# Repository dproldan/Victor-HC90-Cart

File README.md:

# Victor-HC90-Cart
Victor HC-9x adaptor from internal xpansion bus to 50 pin cartridge slot

This has not been manufactured yet.

This is a reproduction from a PCB picture posted here:
https://www.msx.org/forum/msx-talk/hardware/what-is-this-victor-hc-9x-home-made-extension-card-used-for

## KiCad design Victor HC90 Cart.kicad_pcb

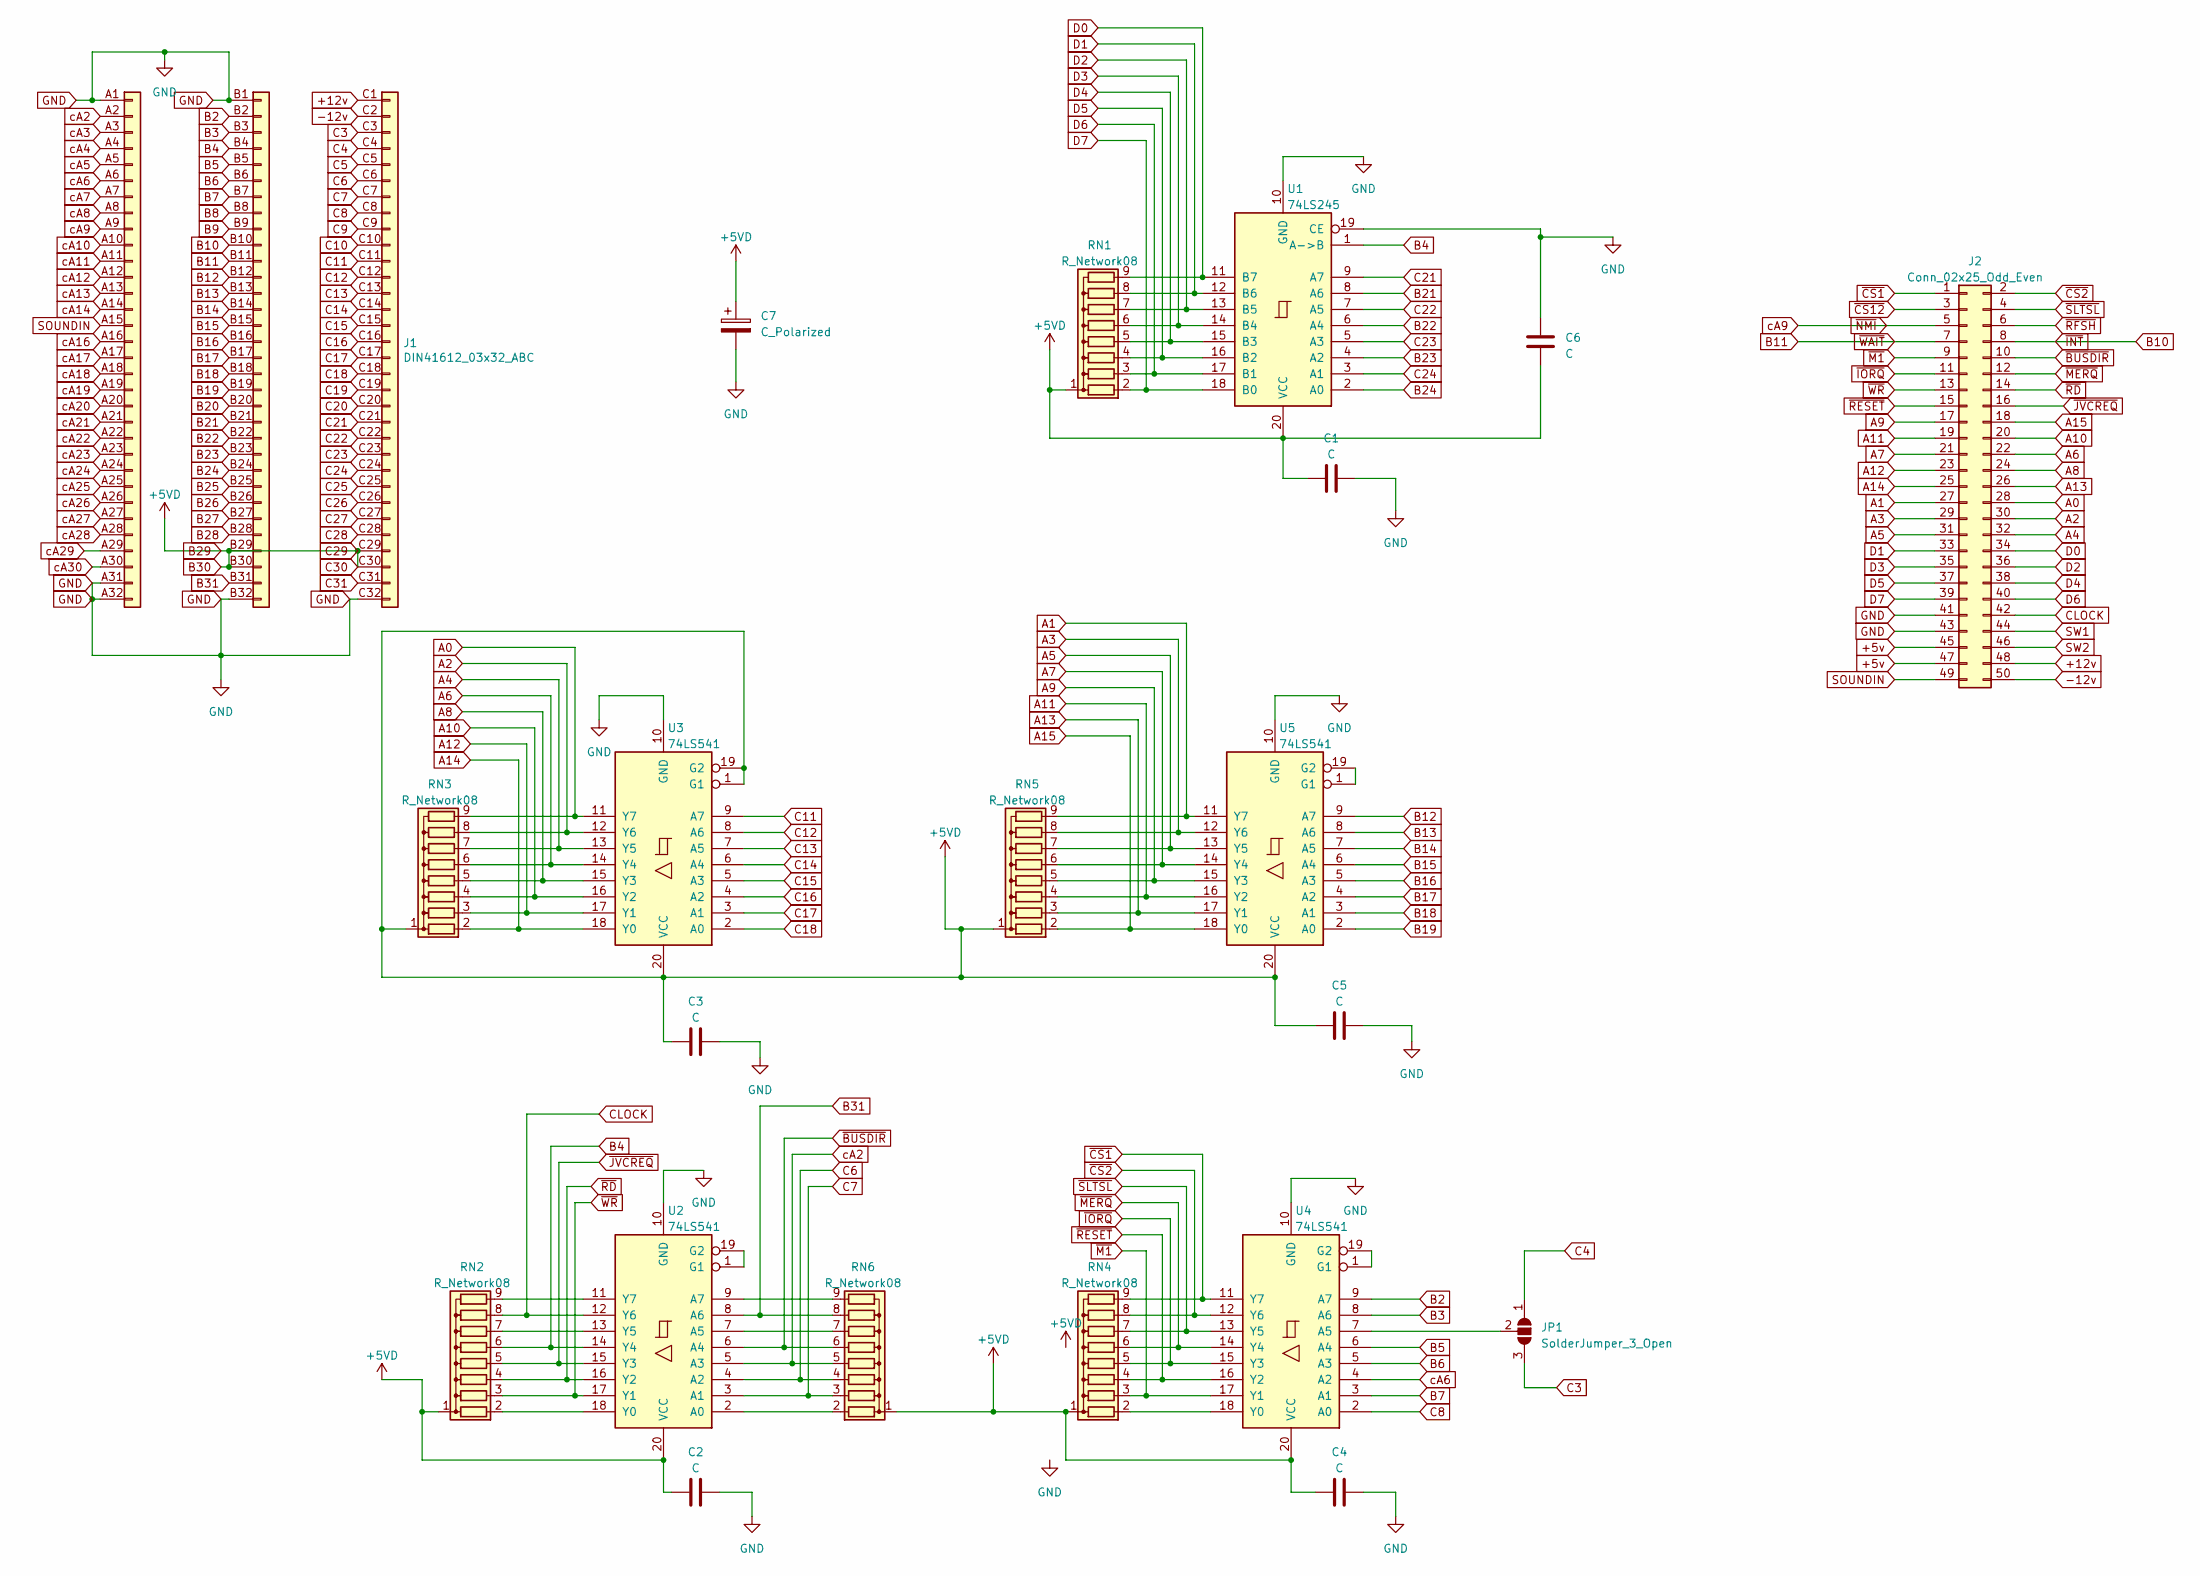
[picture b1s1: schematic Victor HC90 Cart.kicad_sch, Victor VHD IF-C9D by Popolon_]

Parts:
C1, C2, C3, C4, C5, C6: C; C_Disc_D4.3mm_W1.9mm_P5.00mm
C7: C_Polarized; CP_Radial_D8.0mm_P2.50mm
J1: DIN41612_03x32_ABC; Conn_DIN41612_B096F
J2: Conn_02x25_Odd_Even; IDC-Header_2x25_P2.54mm_Latch_Horizontal
JP1: SolderJumper_3_Open; SolderJumper-3_P1.3mm_Open_RoundedPad1.0x1.5mm
RN1, RN2, RN3, RN4, RN5, RN6: R_Network08; R_Array_SIP9
U1: 74LS245; DIP-20_W7.62mm_LongPads
U2, U3, U4, U5: 74LS541; DIP-20_W7.62mm_LongPads

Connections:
+5v: J2.45, J2.47
+12v: J1.C1 (Pin_c1), J2.48
-12v: J1.C2 (Pin_c2), J2.50
A0: J2.28, RN3.9 (R8), U3.11 (Y7)
A1: J2.27, RN5.9 (R8), U5.11 (Y7)
A2: J2.30, RN3.8 (R7), U3.12 (Y6)
A3: J2.29, RN5.8 (R7), U5.12 (Y6)
A4: J2.32, RN3.7 (R6), U3.13 (Y5)
A5: J2.31, RN5.7 (R6), U5.13 (Y5)
A6: J2.22, RN3.6 (R5), U3.14 (Y4)
A7: J2.21, RN5.6 (R5), U5.14 (Y4)
A8: J2.24, RN3.5 (R4), U3.15 (Y3)
A9: J2.17, RN5.5 (R4), U5.15 (Y3)
A10: J2.20, RN3.4 (R3), U3.16 (Y2)
A11: J2.19, RN5.4 (R3), U5.16 (Y2)
A12: J2.23, RN3.3 (R2), U3.17 (Y1)
A13: J2.26, RN5.3 (R2), U5.17 (Y1)
A14: J2.25, RN3.2 (R1), U3.18 (Y0)
A15: J2.18, RN5.2 (R1), U5.18 (Y0)
B2: J1.B2 (Pin_b2), U4.9 (A7)
B3: J1.B3 (Pin_b3), U4.8 (A6)
B4: J1.B4 (Pin_b4), RN2.6 (R5), U1.1 (A->B), U2.14 (Y4)
B5: J1.B5 (Pin_b5), U4.6 (A4)
B6: J1.B6 (Pin_b6), U4.5 (A3)
B7: J1.B7 (Pin_b7), U4.3 (A1)
B8: J1.B8 (Pin_b8)
B9: J1.B9 (Pin_b9)
B10: J1.B10 (Pin_b10), J2.8
B11: J1.B11 (Pin_b11), J2.7
B12: J1.B12 (Pin_b12), U5.9 (A7)
B13: J1.B13 (Pin_b13), U5.8 (A6)
B14: J1.B14 (Pin_b14), U5.7 (A5)
B15: J1.B15 (Pin_b15), U5.6 (A4)
B16: J1.B16 (Pin_b16), U5.5 (A3)
B17: J1.B17 (Pin_b17), U5.4 (A2)
B18: J1.B18 (Pin_b18), U5.3 (A1)
B19: J1.B19 (Pin_b19), U5.2 (A0)
B20: J1.B20 (Pin_b20)
B21: J1.B21 (Pin_b21), U1.8 (A6)
B22: J1.B22 (Pin_b22), U1.6 (A4)
B23: J1.B23 (Pin_b23), U1.4 (A2)
B24: J1.B24 (Pin_b24), U1.2 (A0)
B25: J1.B25 (Pin_b25)
B26: J1.B26 (Pin_b26)
B27: J1.B27 (Pin_b27)
B28: J1.B28 (Pin_b28)
B29: C1.1, C2.1, C3.1, C4.1, C5.1, C6.1, C7.1, J1.B29 (Pin_b29), J1.B30 (Pin_b30), J1.C29 (Pin_c29), J1.C30 (Pin_c30), RN1.1 (common), RN2.1 (common), RN3.1 (common), RN4.1 (common), RN5.1 (common), RN6.1 (common), U1.20 (VCC), U2.20 (VCC), U3.1 (G1), U3.19 (G2), U3.20 (VCC), U4.20 (VCC), U5.20 (VCC)
B31: J1.B31 (Pin_b31), RN6.8 (R7), U2.8 (A6)
C3: J1.C3 (Pin_c3), JP1.3 (B)
C4: J1.C4 (Pin_c4), JP1.1 (A)
C5: J1.C5 (Pin_c5)
C6: J1.C6 (Pin_c6), RN6.4 (R3), U2.4 (A2)
C7: J1.C7 (Pin_c7), RN6.3 (R2), U2.3 (A1)
C8: J1.C8 (Pin_c8), U4.2 (A0)
C9: J1.C9 (Pin_c9)
C10: J1.C10 (Pin_c10)
C11: J1.C11 (Pin_c11), U3.9 (A7)
C12: J1.C12 (Pin_c12), U3.8 (A6)
C13: J1.C13 (Pin_c13), U3.7 (A5)
C14: J1.C14 (Pin_c14), U3.6 (A4)
C15: J1.C15 (Pin_c15), U3.5 (A3)
C16: J1.C16 (Pin_c16), U3.4 (A2)
C17: J1.C17 (Pin_c17), U3.3 (A1)
C18: J1.C18 (Pin_c18), U3.2 (A0)
C19: J1.C19 (Pin_c19)
C20: J1.C20 (Pin_c20)
C21: J1.C21 (Pin_c21), U1.9 (A7)
C22: J1.C22 (Pin_c22), U1.7 (A5)
C23: J1.C23 (Pin_c23), U1.5 (A3)
C24: J1.C24 (Pin_c24), U1.3 (A1)
C25: J1.C25 (Pin_c25)
C26: J1.C26 (Pin_c26)
C27: J1.C27 (Pin_c27)
C28: J1.C28 (Pin_c28)
C31: J1.C31 (Pin_c31)
CLOCK: J2.42, RN2.8 (R7), U2.12 (Y6)
D0: J2.34, RN1.9 (R8), U1.11 (B7)
D1: J2.33, RN1.8 (R7), U1.12 (B6)
D2: J2.36, RN1.7 (R6), U1.13 (B5)
D3: J2.35, RN1.6 (R5), U1.14 (B4)
D4: J2.38, RN1.5 (R4), U1.15 (B3)
D5: J2.37, RN1.4 (R3), U1.16 (B2)
D6: J2.40, RN1.3 (R2), U1.17 (B1)
D7: J2.39, RN1.2 (R1), U1.18 (B0)
GND: C1.2, C2.2, C3.2, C4.2, C5.2, C6.2, C7.2, J1.A1 (Pin_a1), J1.A31 (Pin_a31), J1.A32 (Pin_a32), J1.B1 (Pin_b1), J1.B32 (Pin_b32), J1.C32 (Pin_c32), J2.41, J2.43, U1.10 (GND), U1.19 (CE), U2.10 (GND), U3.10 (GND), U4.10 (GND), U5.10 (GND)
unnamed: JP1.2 (C), U4.7 (A5)
unnamed: RN2.2 (R1), U2.18 (Y0)
unnamed: RN2.7 (R6), U2.13 (Y5)
unnamed: RN2.9 (R8), U2.11 (Y7)
unnamed: RN4.2 (R1), U4.18 (Y0)
unnamed: RN6.2 (R1), U2.2 (A0)
unnamed: RN6.7 (R6), U2.7 (A5)
unnamed: RN6.9 (R8), U2.9 (A7)
unnamed: U2.1 (G1), U2.19 (G2)
unnamed: U4.1 (G1), U4.19 (G2)
unnamed: U5.1 (G1), U5.19 (G2)
SOUNDIN: J1.A15 (Pin_a15), J2.49
SW1: J2.44
SW2: J2.46
cA2: J1.A2 (Pin_a2), RN6.5 (R4), U2.5 (A3)
cA3: J1.A3 (Pin_a3)
cA4: J1.A4 (Pin_a4)
cA5: J1.A5 (Pin_a5)
cA6: J1.A6 (Pin_a6), U4.4 (A2)
cA7: J1.A7 (Pin_a7)
cA8: J1.A8 (Pin_a8)
cA9: J1.A9 (Pin_a9), J2.5
cA10: J1.A10 (Pin_a10)
cA11: J1.A11 (Pin_a11)
cA12: J1.A12 (Pin_a12)
cA13: J1.A13 (Pin_a13)
cA14: J1.A14 (Pin_a14)
cA16: J1.A16 (Pin_a16)
cA17: J1.A17 (Pin_a17)
cA18: J1.A18 (Pin_a18)
cA19: J1.A19 (Pin_a19)
cA20: J1.A20 (Pin_a20)
cA21: J1.A21 (Pin_a21)
cA22: J1.A22 (Pin_a22)
cA23: J1.A23 (Pin_a23)
cA24: J1.A24 (Pin_a24)
cA25: J1.A25 (Pin_a25)
cA26: J1.A26 (Pin_a26)
cA27: J1.A27 (Pin_a27)
cA28: J1.A28 (Pin_a28)
cA29: J1.A29 (Pin_a29)
cA30: J1.A30 (Pin_a30)
~BUSDIR: J2.10, RN6.6 (R5), U2.6 (A4)
~CS1: J2.1, RN4.9 (R8), U4.11 (Y7)
~CS2: J2.2, RN4.8 (R7), U4.12 (Y6)
~CS12: J2.3
~IORQ: J2.11, RN4.5 (R4), U4.15 (Y3)
~JVCREQ: J2.16, RN2.5 (R4), U2.15 (Y3)
~M1: J2.9, RN4.3 (R2), U4.17 (Y1)
~MERQ: J2.12, RN4.6 (R5), U4.14 (Y4)
~RD: J2.14, RN2.4 (R3), U2.16 (Y2)
~RESET: J2.15, RN4.4 (R3), U4.16 (Y2)
~RFSH: J2.6
~SLTSL: J2.4, RN4.7 (R6), U4.13 (Y5)
~WR: J2.13, RN2.3 (R2), U2.17 (Y1)

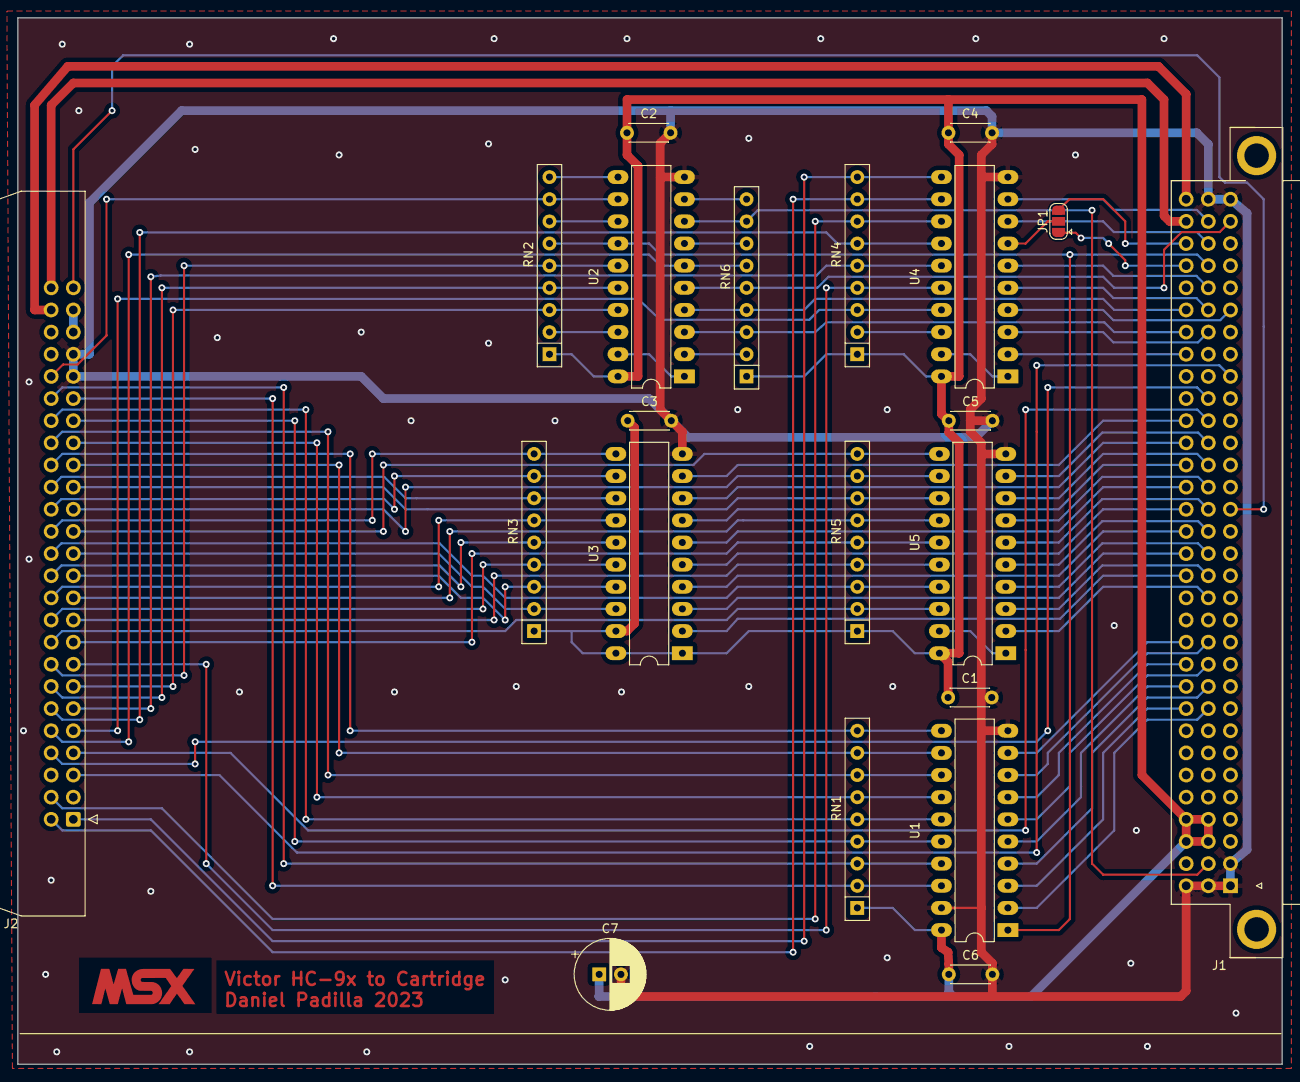
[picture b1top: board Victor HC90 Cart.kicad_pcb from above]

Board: 2 copper layers, 145.0 x 120.0 mm, 21 parts (0 on the bottom side), 94 nets.

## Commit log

2023-04-02 Initial upload
    First upload, not tested.
2023-04-02 added PCB views
